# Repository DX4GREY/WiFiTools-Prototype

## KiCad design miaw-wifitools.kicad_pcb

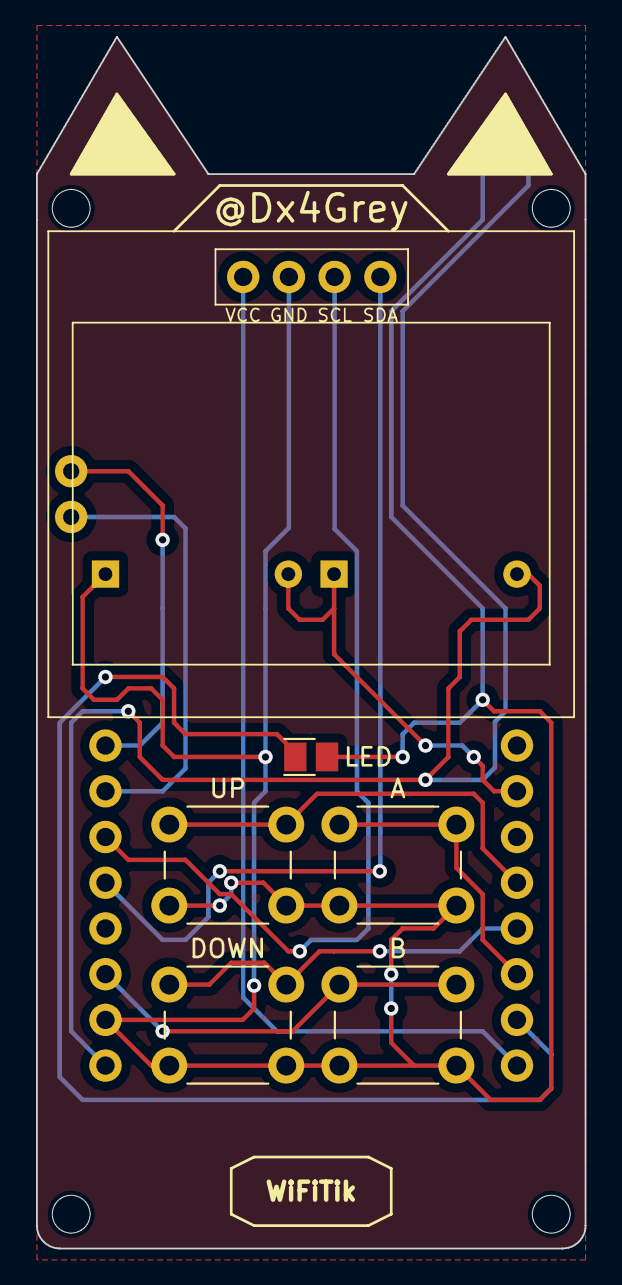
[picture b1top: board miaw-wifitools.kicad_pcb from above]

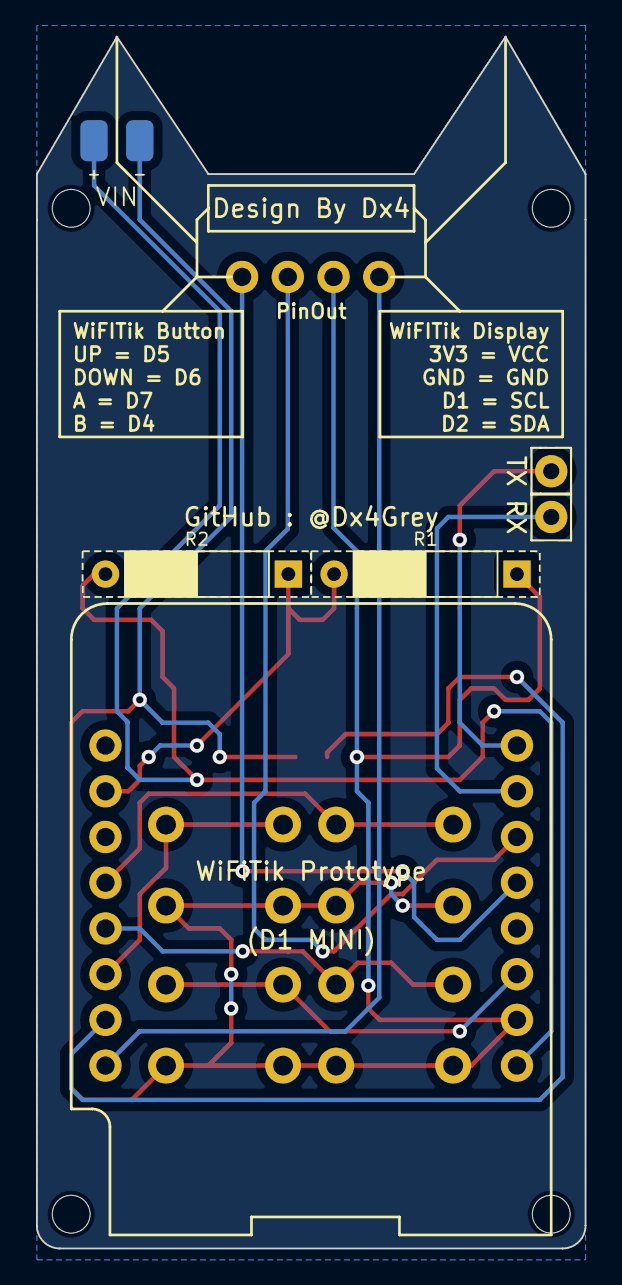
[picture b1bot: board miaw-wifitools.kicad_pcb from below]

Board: 2 copper layers, 30.5 x 67.3 mm, 15 parts (6 on the bottom side), 10 nets.

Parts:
(D1 MINI): Wemos-D1-mini; wemos-d1-mini-connectors-only
A: SW_PUSH_6mm
B: SW_PUSH_6mm
DOWN: SW_PUSH_6mm
Hole: MountingHole_2.1mm
Hole#2, Hole#3, Hole#4: MountingHole_2.1mm
LED: LED_Cree-XQ_HandSoldering
R1, R2: Resistor
RX: Pin_D0.9mm_L10.0mm_W2.4mm_FlatFork
TX: Pin_D0.9mm_L10.0mm_W2.4mm_FlatFork
UP: SW_PUSH_6mm
VIN: Power 5V

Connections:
/5V5: (D1 MINI).9, R2.1, VIN.1
/A: (D1 MINI).6, A.1
/B: (D1 MINI).11, B.1
/BATLEVEL: (D1 MINI).2, R1.1, R2.2
/DOWN: (D1 MINI).5, DOWN.1
/GND: (D1 MINI).10, A.2, B.2, DOWN.2, LED.2, R1.2, UP.2, VIN.2
/LED: (D1 MINI).7, LED.1
/RX: (D1 MINI).15, RX.1
/TX: (D1 MINI).16, TX.1
/UP: (D1 MINI).4, UP.1

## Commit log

2023-12-18 Update gerber
